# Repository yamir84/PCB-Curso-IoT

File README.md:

# PCB-Curso-IoT

- Archivos para armar el PCB del proyecto.

Archivo: demoplacaV2.lay6 
Diseño en Sprint Layots6 , lo pueden descargar del siguiente link: https://tinyurl.com/upk8nqq
https://cubaelectronica.blogspot.com/2017/06/descarga-de-sprint-layout-60.html

Los demas archivos son para el uso en KiCAD.

- Imagenes de Captura de los PCB en el Sprint Layout.

Archivos del esquema del plano y PCB para uso con el metodo de Planchado.

CubaElectronica.
freeiot.tk

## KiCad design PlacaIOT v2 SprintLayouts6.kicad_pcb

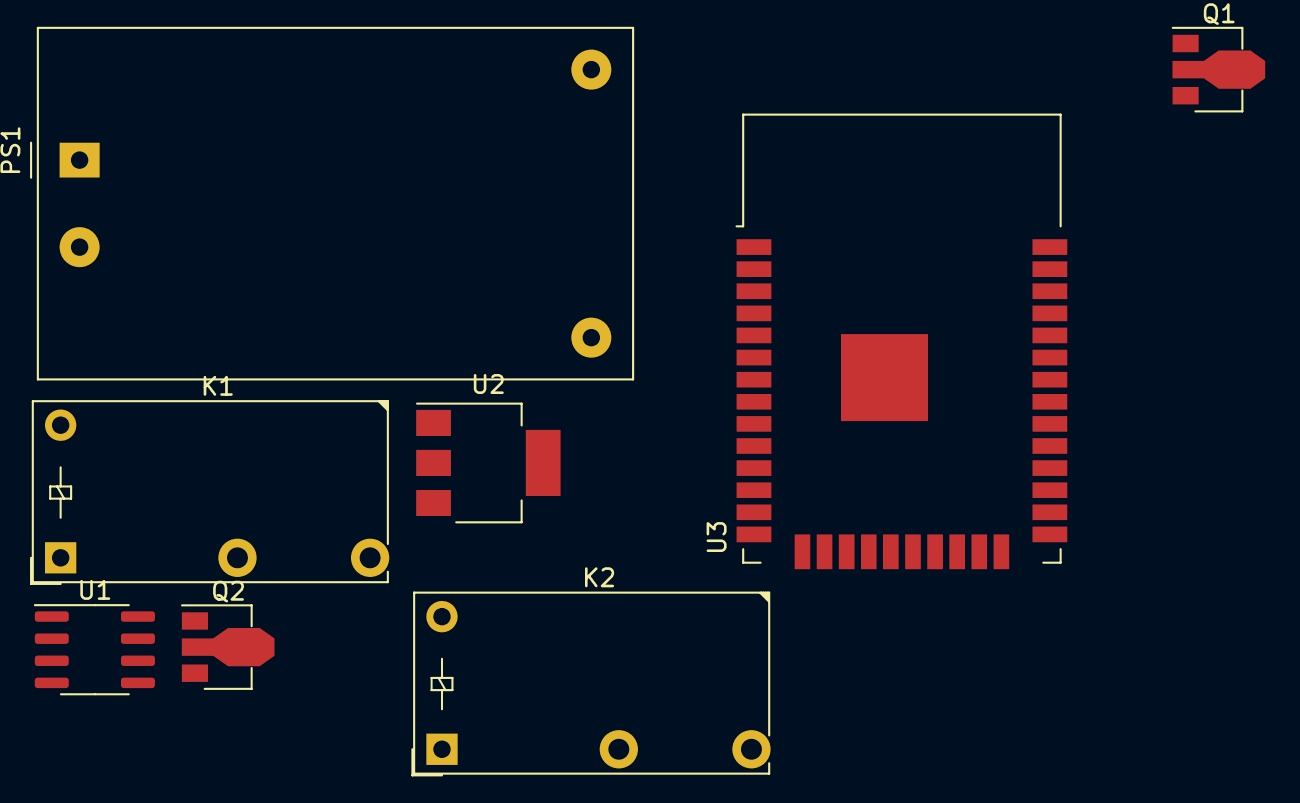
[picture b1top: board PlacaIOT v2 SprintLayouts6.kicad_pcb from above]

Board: 2 copper layers, 8 parts (0 on the bottom side), 7 nets, no tracks yet.

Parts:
K1: RELAY1; Relay_SPST_Finder_32.21-x300
K2: RELAY2; Relay_SPST_Finder_32.21-x300
PS1: HLK-PM01; Converter_ACDC_HiLink_HLK-PMxx
Q1: BCX56; SOT-89-3
Q2: BC546; SOT-89-3
U1: ACS712xLCTR-05B; SOIC-8_3.9x4.9mm_P1.27mm
U2: AP1117-33; SOT-223-3_TabPin2
U3: ESP32-WROOM-32D; ESP32-WROOM-32

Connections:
+3V3: U2.2, U3.2
+5V: K1.A2, K2.A2, PS1.4, U1.8, U2.3
GND: PS1.3, Q1.3, Q2.3, U1.5, U2.1, U3.1, U3.15, U3.38, U3.39
unnamed: K2.A1, Q2.2
unnamed: K1.A1, Q1.2
unnamed: PS1.2, U1.1, U1.2
unnamed: K1.11, U1.3, U1.4

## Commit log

2020-04-08 primer commit
